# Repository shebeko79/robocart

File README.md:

### How not to build a robot:

https://youtu.be/LK63FLP5XUo

### References:
[Field Oriented Control (FOC) for stock hoverboards](https://github.com/EFeru/hoverboard-firmware-hack-FOC)

[Introduction to MaixCAM](https://wiki.sipeed.com/hardware/en/maixcam/maixcam.html)

[MaixCAM System Flashing](https://wiki.sipeed.com/hardware/en/maixcam/os.html)

[MaixPy Quick Start](https://wiki.sipeed.com/maixpy/doc/en/index.html)

[Install RNDIS driver](https://wiki.sipeed.com/hardware/en/maixsense/maixsense-a075v/install_drivers.html)

[Ultralytics quick start](https://docs.ultralytics.com/usage/python/)

[Tracking with Ultralytics](https://docs.ultralytics.com/modes/track/)

[FastSAM](https://docs.ultralytics.com/models/fast-sam/)

[Labeling Application](https://github.com/shebeko79/py_misc/tree/main/yolo_labeling)

[My YOLO train notes](https://github.com/shebeko79/py_misc/tree/main/yolo_train)

[Self-learning Tracker](https://wiki.sipeed.com/maixpy/doc/en/vision/self_learn_detector.html)

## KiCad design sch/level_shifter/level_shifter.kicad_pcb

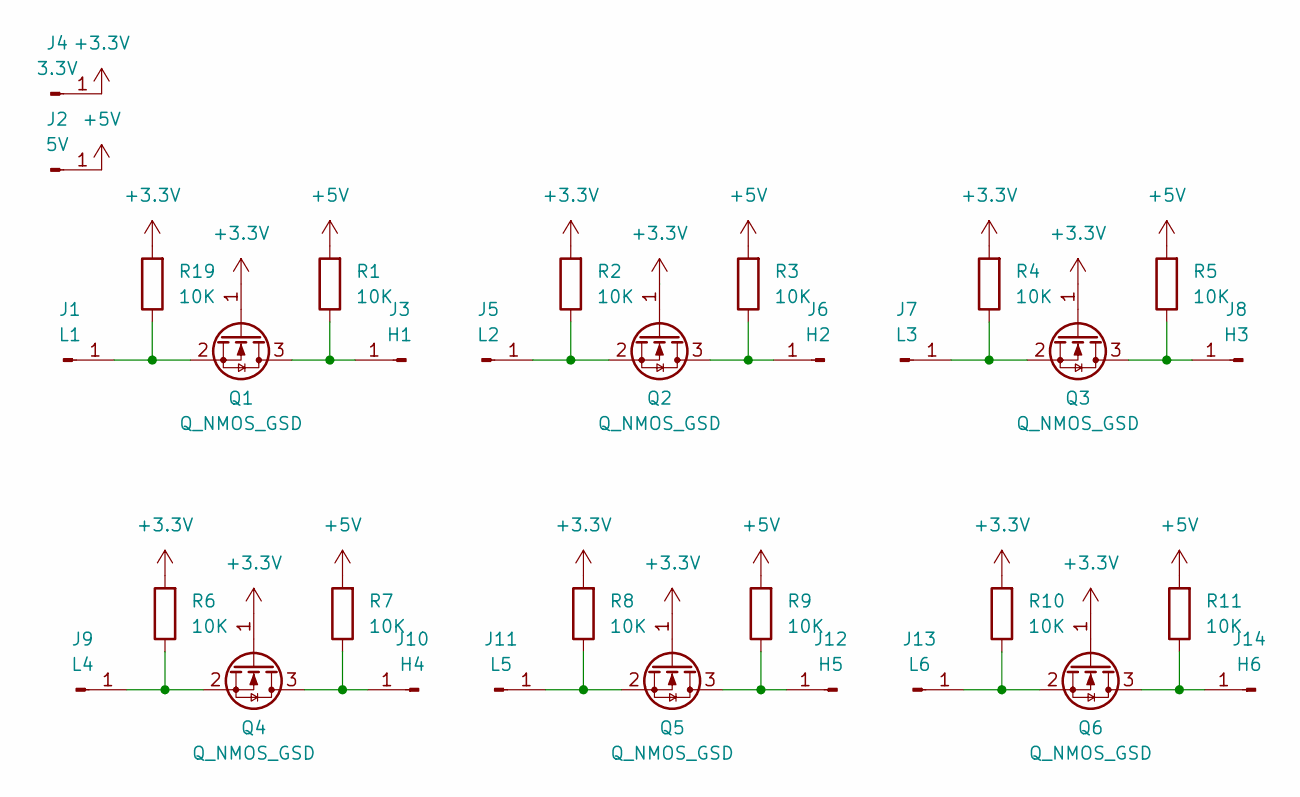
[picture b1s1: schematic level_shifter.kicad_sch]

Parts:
J1: L1; SolderWirePad_1x01_SMD_1x2mm
J2: 5V; SolderWirePad_1x01_SMD_1x2mm
J3: H1; SolderWirePad_1x01_SMD_1x2mm
J4: 3.3V; SolderWirePad_1x01_SMD_1x2mm
J5: L2; SolderWirePad_1x01_SMD_1x2mm
J6: H2; SolderWirePad_1x01_SMD_1x2mm
J7: L3; SolderWirePad_1x01_SMD_1x2mm
J8: H3; SolderWirePad_1x01_SMD_1x2mm
J9: L4; SolderWirePad_1x01_SMD_1x2mm
J10: H4; SolderWirePad_1x01_SMD_1x2mm
J11: L5; SolderWirePad_1x01_SMD_1x2mm
J12: H5; SolderWirePad_1x01_SMD_1x2mm
J13: L6; SolderWirePad_1x01_SMD_1x2mm
J14: H6; SolderWirePad_1x01_SMD_1x2mm
Q1, Q2, Q3, Q4, Q5, Q6: Q_NMOS_GSD; SOT-23_Handsoldering
R1, R2, R3, R4, R5, R6, R7, R8, R9, R10, R11, R19: 10K; R_0805_2012Metric

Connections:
+3.3V: J4.1, Q1.1 (G), Q2.1 (G), Q3.1 (G), Q4.1 (G), Q5.1 (G), Q6.1 (G), R2.2, R4.2, R6.2, R8.2, R10.2, R19.2
+5V: J2.1, R1.2, R3.2, R5.2, R7.2, R9.2, R11.2
unnamed: J1.1, Q1.2 (S), R19.1
unnamed: J3.1, Q1.3 (D), R1.1
unnamed: J5.1, Q2.2 (S), R2.1
unnamed: J6.1, Q2.3 (D), R3.1
unnamed: J7.1, Q3.2 (S), R4.1
unnamed: J8.1, Q3.3 (D), R5.1
unnamed: J9.1, Q4.2 (S), R6.1
unnamed: J10.1, Q4.3 (D), R7.1
unnamed: J11.1, Q5.2 (S), R8.1
unnamed: J12.1, Q5.3 (D), R9.1
unnamed: J13.1, Q6.2 (S), R10.1
unnamed: J14.1, Q6.3 (D), R11.1

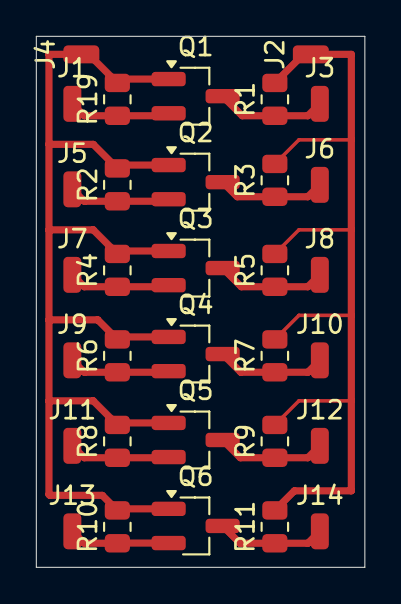
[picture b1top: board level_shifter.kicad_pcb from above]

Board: 4 copper layers, 18.2 x 29.5 mm, 32 parts (0 on the bottom side), 14 nets.

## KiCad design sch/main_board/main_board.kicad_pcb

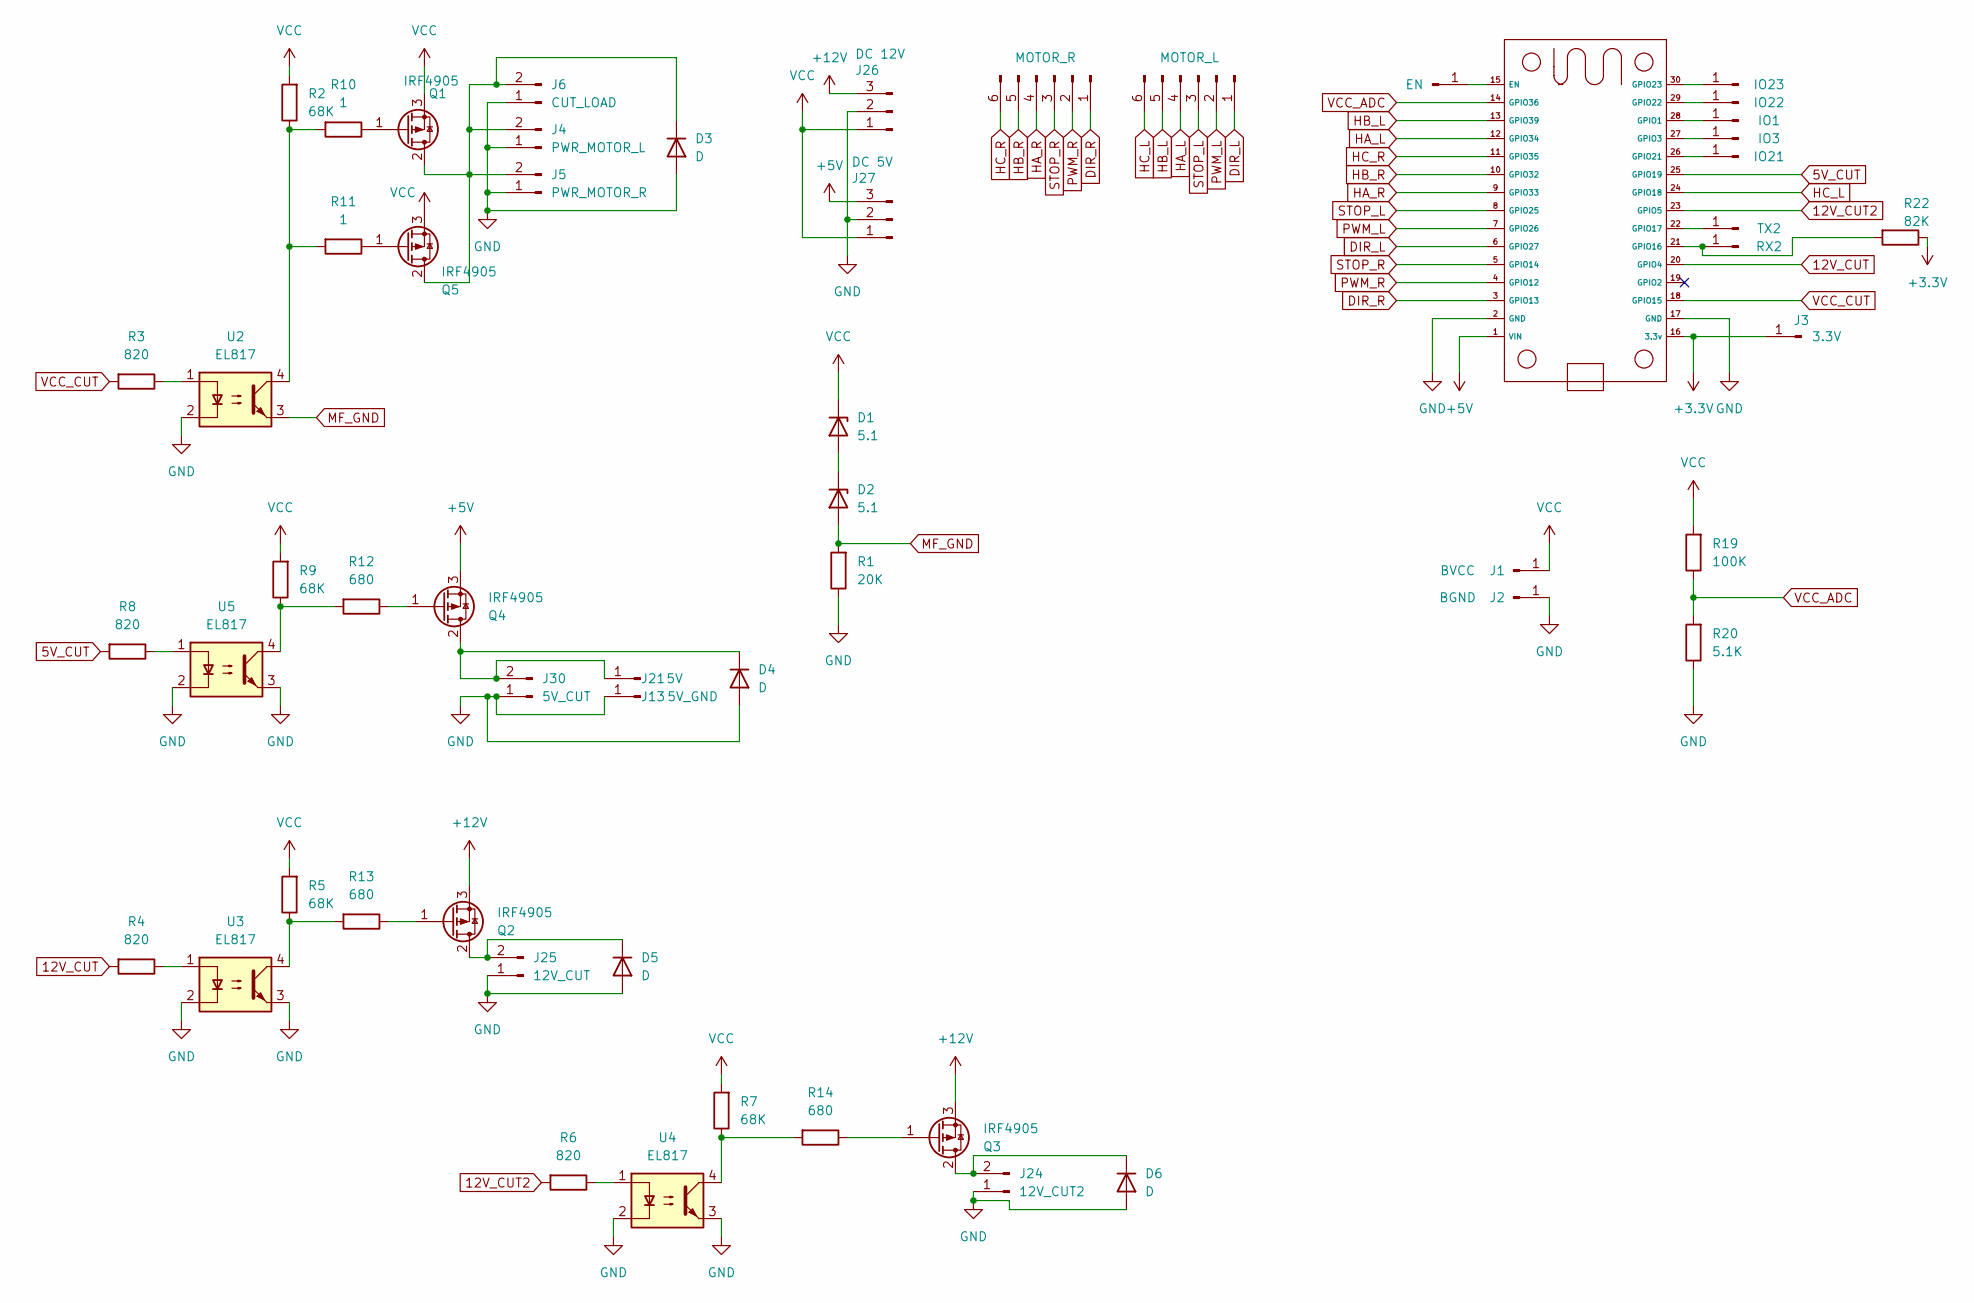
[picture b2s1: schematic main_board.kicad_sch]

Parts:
D1, D2: 5.1; D_5W_P12.70mm_Horizontal
D3, D4, D5, D6: D; D_2010_5025Metric_Pad1.52x2.65mm_HandSolder
J1: BVCC; SolderWirePad_1x01_SMD_4x8mm
J2: BGND; SolderWirePad_1x01_SMD_4x8mm
J3: 3.3V; SolderWirePad_1x01_SMD_2x4mm
J4: PWR_MOTOR_L; SolderWire-2.5sqmm_1x02_P7.2mm_D2.4mm_OD3.6mm
J5: PWR_MOTOR_R; SolderWire-2.5sqmm_1x02_P7.2mm_D2.4mm_OD3.6mm
J6: CUT_LOAD; SolderWire-2.5sqmm_1x02_P7.2mm_D2.4mm_OD3.6mm
J7: MOTOR_R; JST_XH_B6B-XH-A_1x06_P2.50mm_Vertical
J8: MOTOR_L; JST_XH_B6B-XH-A_1x06_P2.50mm_Vertical
J9: EN; SolderWirePad_1x01_SMD_1.5x3mm
J13: 5V_GND; SolderWirePad_1x01_SMD_2x4mm
J14: IO23; SolderWirePad_1x01_SMD_1.5x3mm
J15: IO22; SolderWirePad_1x01_SMD_1.5x3mm
J16: IO1; SolderWirePad_1x01_SMD_1.5x3mm
J17: IO3; SolderWirePad_1x01_SMD_1.5x3mm
J18: IO21; SolderWirePad_1x01_SMD_1.5x3mm
J21: 5V; SolderWirePad_1x01_SMD_2x4mm
J22: TX2; SolderWirePad_1x01_SMD_1.5x3mm
J23: RX2; SolderWirePad_1x01_SMD_1.5x3mm
J24: 12V_CUT2; SolderWire-1sqmm_1x02_P5.4mm_D1.4mm_OD2.7mm
J25: 12V_CUT; SolderWire-1sqmm_1x02_P5.4mm_D1.4mm_OD2.7mm
J26: DC 12V; SolderWire-1.5sqmm_1x03_P6mm_D1.7mm_OD3mm
J27: DC 5V; SolderWire-1.5sqmm_1x03_P6mm_D1.7mm_OD3mm
J30: 5V_CUT; SolderWire-1sqmm_1x02_P5.4mm_D1.4mm_OD2.7mm
Q1, Q2, Q3, Q4, Q5: IRF4905; TO-220-3_Vertical
R1: 20K; R_0805_2012Metric
R2, R5, R7, R9: 68K; R_0805_2012Metric
R3, R4, R6, R8: 820; R_0805_2012Metric
R10, R11: 1; R_0805_2012Metric
R12, R13, R14: 680; R_0805_2012Metric
R19: 100K; R_0805_2012Metric
R20: 5.1K; R_0805_2012Metric
R22: 82K; R_0805_2012Metric
U1: ESP32_30pin
U2, U3, U4, U5: EL817; SMDIP-4_W9.53mm

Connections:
5V_CUT: R8.2, U1.25 (GPIO19)
12V_CUT: R4.2, U1.20 (GPIO4)
12V_CUT2: R6.2, U1.23 (GPIO5)
+3.3V: J3.1, R22.1, U1.16 (3.3v)
+5V: J27.3, Q4.3 (S), U1.1 (VIN)
+12V: J26.3, Q2.3 (S), Q3.3 (S)
DIR_L: J8.1, U1.6 (GPIO27)
DIR_R: J7.1, U1.3 (GPIO13)
GND: D3.2 (A), D4.2 (A), D5.2 (A), D6.2 (A), J2.1, J4.1, J5.1, J6.1, J13.1, J24.1, J25.1, J26.2, J27.2, J30.1, R1.1, R20.1, U1.2 (GND), U1.17 (GND), U2.2, U3.2, U3.3, U4.2, U4.3, U5.2, U5.3
HA_L: J8.4, U1.12 (GPIO34)
HA_R: J7.4, U1.9 (GPIO33)
HB_L: J8.5, U1.13 (GPIO39)
HB_R: J7.5, U1.10 (GPIO32)
HC_L: J8.6, U1.24 (GPIO18)
HC_R: J7.6, U1.11 (GPIO35)
MF_GND: D2.2 (A), R1.2, U2.3
unnamed: D1.2 (A), D2.1 (K)
unnamed: D3.1 (K), J4.2, J5.2, J6.2, Q1.2 (D), Q5.2 (D)
unnamed: D4.1 (K), J21.1, J30.2, Q4.2 (D)
unnamed: D5.1 (K), J25.2, Q2.2 (D)
unnamed: D6.1 (K), J24.2, Q3.2 (D)
unnamed: J9.1, U1.15 (EN)
unnamed: J14.1, U1.30 (GPIO23)
unnamed: J15.1, U1.29 (GPIO22)
unnamed: J16.1, U1.28 (GPIO1)
unnamed: J17.1, U1.27 (GPIO3)
unnamed: J18.1, U1.26 (GPIO21)
unnamed: J22.1, U1.22 (GPIO17)
unnamed: J23.1, R22.2, U1.21 (GPIO16)
unnamed: Q1.1 (G), R10.1
unnamed: Q2.1 (G), R13.1
unnamed: Q3.1 (G), R14.1
unnamed: Q4.1 (G), R12.1
unnamed: Q5.1 (G), R11.1
unnamed: R3.1, U2.1
unnamed: R4.1, U3.1
unnamed: R6.1, U4.1
unnamed: R8.1, U5.1
unnamed: R2.1, R10.2, R11.2, U2.4
unnamed: R9.1, R12.2, U5.4
unnamed: R5.1, R13.2, U3.4
unnamed: R7.1, R14.2, U4.4
PWM_L: J8.2, U1.7 (GPIO26)
PWM_R: J7.2, U1.4 (GPIO12)
STOP_L: J8.3, U1.8 (GPIO25)
STOP_R: J7.3, U1.5 (GPIO14)
VCC: D1.1 (K), J1.1, J26.1, J27.1, Q1.3 (S), Q5.3 (S), R2.2, R5.2, R7.2, R9.2, R19.2
VCC_ADC: R19.1, R20.2, U1.14 (GPIO36)
VCC_CUT: R3.2, U1.18 (GPIO15)

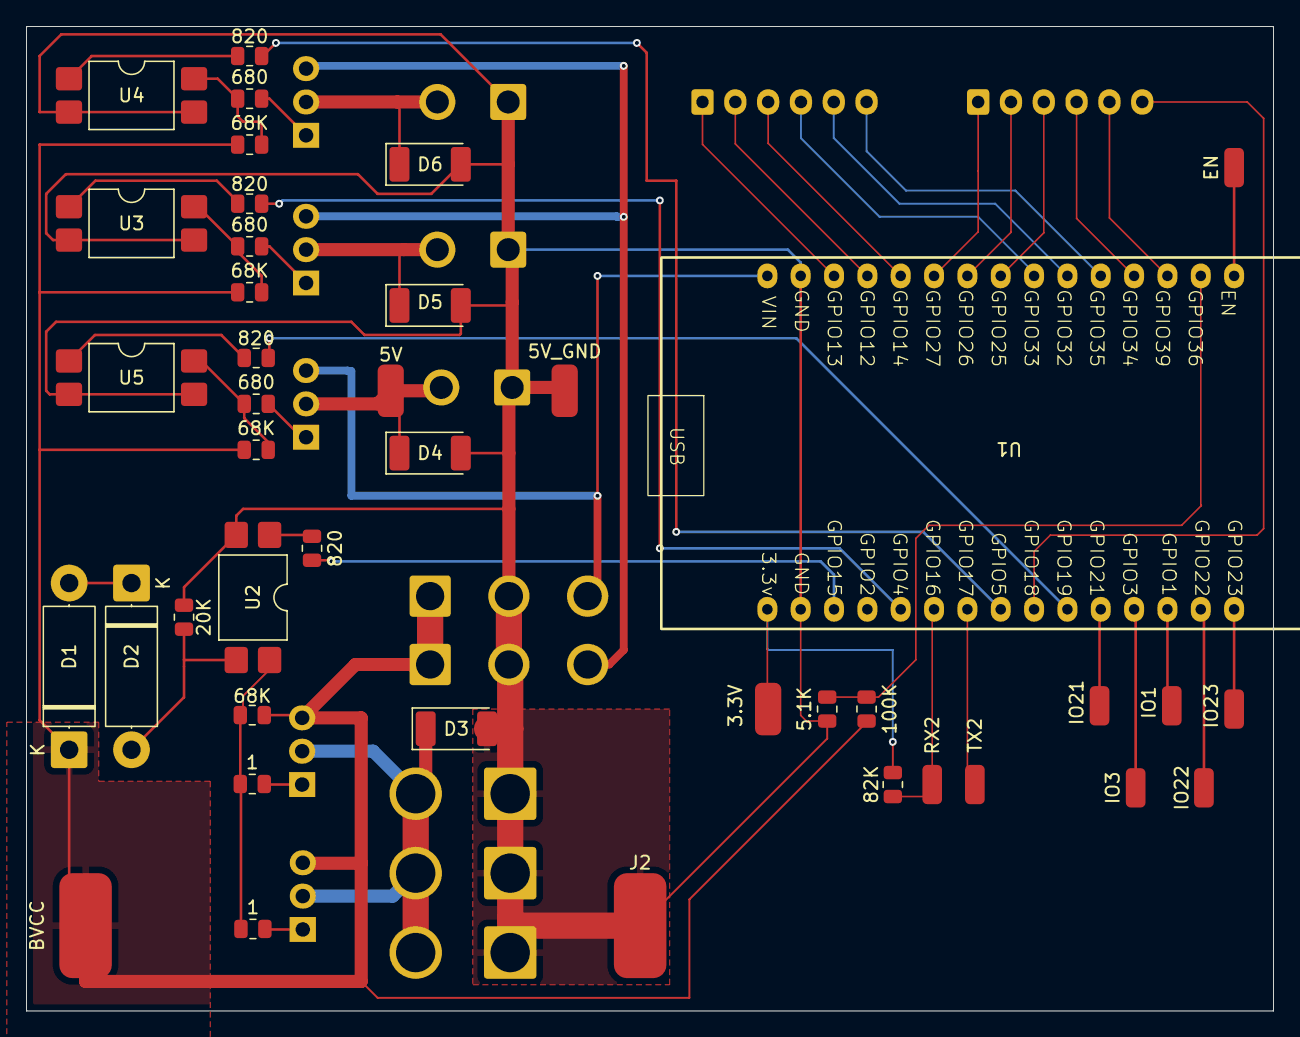
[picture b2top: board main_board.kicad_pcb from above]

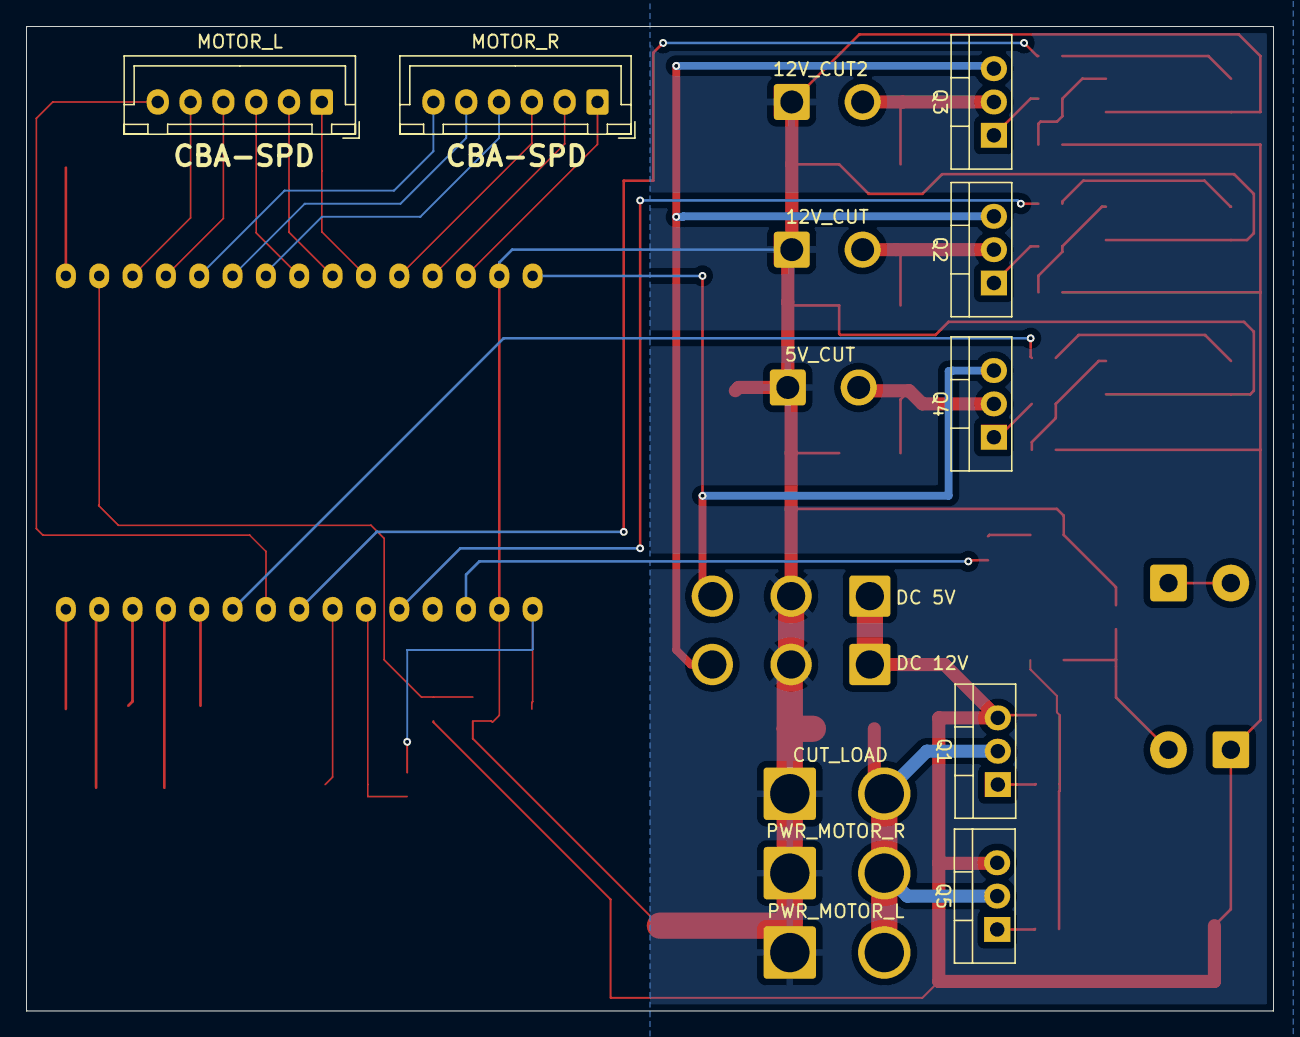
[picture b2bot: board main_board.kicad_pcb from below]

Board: 2 copper layers, 95.0 x 75.0 mm, 56 parts (15 on the bottom side), 49 nets.

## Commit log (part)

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2024-08-30 2 wheel platform based on esp32
2024-09-20 Bluetooth remote control
2024-09-28 Add "block" command in BT remote control
2024-09-28 Examples files for maixcam
2024-10-05 Implementing state machine for UI
2024-10-06 Implement button click and rectangle selection
2024-10-06 Add rectangle normalization
2024-10-07 Add MoveTo algo.
2024-10-12 returns image each second on web
2024-10-12 Add buttons using ChatGPT
2024-10-12 chatGPT image click
2024-10-12 chatGPT select rectangle
2024-10-12 1. Prevent rectangle visible until object selection (chatGPT) 2. Prevent dragging image (chatGPT) 3. Process requests on server side 4. Prevent crash, when to_jpeg() returns None after script restart
2024-10-12 Add just move states
2024-10-13 Mobile adaptation for select rectangle (chatGPT)
2024-10-13 Click on image for mobile (chatGPT)
2024-10-13 Move buttons to right
2024-10-13 Rename move states for vertical alignment Load main html from BASE_PATH path
2024-10-15 Add WiFi features. If fail connect to WiFi switch to AP mode
2024-10-19 Configuring network thru python was bad idea. Add S30wifidyn which try establish sta connection, if fails switch to ap mode
2024-10-19 Shrink move state to fit on a screen More robust S81robot stop function
2024-10-27 1. Get rid of Flask, because it creates a lot of threads and to noisy 2. Implement synchronized function call in main thread. 3. Get state just after click,click_point, sel_rect requests
2024-10-27 1. Apply immediately /click /click_point /sel_rect to buttons state 2. Return state even if requests are not executed 3. Move server to 80 port
2024-11-09 Increase line width to avoid red-grey rectangles
2024-11-19 pan\tilt stl model
2024-12-08 Parts schematic
2024-12-08 Test of zs-x11h controller
2024-12-09 rename motor.h to mdd3a controller which was used to control dc motor
2024-12-10 1. Move to PlatformIO 2. Speed measurement
2024-12-11 Connect brake pin
2024-12-12 Add PID control
2024-12-12 Change remote to relative protocol
2024-12-12 Add relative protocol
2024-12-13 1. Always brake for zero speed 2. 20kHz PWM just follow controllers recommendations 3. Separate RELATIVE_MAX_SPEED because it a bit scary with full speed 4. Dump wheels state in com port to have a gl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
2024-12-13 command to set maximum relative_speed
2024-12-13 Better command parsing
2024-12-21 Update 3d models 1. Base for pantilt 2. Cover for 2020 profile
2024-12-21 shorter screw placeholer
2024-12-25 Maixcam pinout
2024-12-28 Fix rotation cast
2024-12-28 Change mover to speed and pan
2024-12-31 Add scservo_sdk and pan_tilt example proba/pan_tilt.py all necessary function (i.e. reduce baud rate) which performes thru USB of SCServo controller maix/pan_tilt.py is a sketch for pan-til support
2025-01-01 Implementation of pan-tilt tracking Doesn't work as expected yet
2025-01-01 Add exit state for graceful exit
2025-01-02 Release servos when exit Measure real focus distance
2025-01-04 Full screen image
2025-01-05 1. Use relative (0.0-1.0) image coordinates for tracker 2. Make image full-screen on http page
2025-01-27 rtsp test
2025-01-27 Avoid low power exception on shutdown
2025-01-27 send file feature Potentially unsafe we need to check if file really in assets directory
2025-02-16 PID control on pwm instead of speed
2025-02-16 Split motor_speed.h to .cpp and .h
2025-02-16 Try to make remote more stable
2025-02-16 Assume we have some koef. between PWM and unloaded wheel speed. Make error correction around this value. Also introduced delays. But it doesn't look like it helps somehow. Add maximum acceleration bu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
2025-02-16 Motors control in separate thread
2025-03-08 Speed test with different masses and PWM
2025-03-14 Temoprary checkpoint
2025-03-15 Less or more satisfied. Works pretty much the same for different loads. Like empty truck or me as a load. We don't try to adjust m_speed2pwm because it not constant even for the same environment. In 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
    The general idea now is:
    - adjust PWM slowly unless it increase the speed with any acceleration
    - add one time kick to PWM if speed remain zero
    - break if speed go to far in wrong direction or go with acceleration
2025-03-22 rename timer0 to speed_timer
2025-03-22 Increase pan/tilt insensitive zone to avoid shaking
2025-03-30 Yolo custom model track
2025-04-19 Hide internal tracker structure
2025-04-19 Implement yolo trackers
2025-04-21 Add pan, move, follow tracking modes.
2025-04-21 Caption for tracker selection
2025-04-21 Show click caption and rectangle caption in HTML
2025-04-21 Fix X offset in point and rectangle selection. Wrong condition cause default 640X480 doesn't update to real size 640X640
2025-04-21 Fix nanotrack display on the screen
2025-04-23 1. Pass correct fit to MoveTo 2. Ensure tracker still in the yolo_trackers, because self stopping algo calls YoloTrackObject::stop() 2 times.
2025-09-29 Discover different streaming options
2025-09-29 Kikad board of the robot
2025-10-12 1. Add pins header 2. Add deep sleep on low-voltage
2025-10-13 Tune voltage for another ESP module
2025-10-13 1. Reconnect 5V_CUT from GPIO2 to GPIO19. Because GPIO2 is the LED 2. Pull-up RX2 3. Figured out with VCC_ADC resistor divider 4. Change input to NPN cut transistor from 200 Om to 10K. 200 Om is way 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
2025-10-13 Swap the motors. Simply because it easier to connect
2025-11-16 Final scheme changes before production
2025-11-24 5V <-> 3.3V level shifter schematic Direct 5V on other inputs affects on ADC and we can't get correct voltage
2025-11-24 Smoothing voltage and add delay on low voltage sleep
2025-11-24 I don't use this N-MOSFET anymore
2025-11-25 We can't use GPIO39 for hall input, because it also VN Whenever we measure ADC on GPIO36 (VP) interrupt for GPIO39 is raised
2025-11-25 .kikad_prl is a settings. Don't need to store'em in repository
2025-11-29 Use hall sensors to detect direction of speed
2025-11-29 Move hardware specific from speed controller directly to motor controller
2025-11-29 Add state,sleep,power commands
2025-11-30 Show voltage on a screen and web interface
2025-11-30 Increase a low voltage a bit, because not much energy left even to sleep with previous limit.
2025-12-13 Move touch functionality out of main.py into separate file
2025-12-13 1. Fix: sleep command should receive int parameter 2. Increase sleep duration to 5 min, because unlikely battery charge faster
2025-12-13 Go to sleep on idle
2025-12-13 Add Telegram support
2025-12-14 Seems times updates after start. And because of previous attempt to fix it module doesn't off at all
2025-12-14 Graceful power down
2025-12-14 Save config and last telegram update_id to files
2025-12-14 Need to skip few cycles to let receive the voltage and get stable image
2025-12-14 Adaptive telegram update interval
2025-12-15 Check that commands has been sent from our chat
2025-12-15 Treat telegram commands also as keep alive factor
2025-12-16 fix params duplication for set of commands
2025-12-19 send/receive jpg just throu UDP
2025-12-20 Trying to establish p2p connection. Fails so far
2025-12-25 Start implementing UDP channel
2025-12-28 Start implementing desktop application Fix some bugs in UDP protocol
2025-12-29 First image in the client application
2025-12-31 Switch off http interface
2025-12-31 Change default net name to "robocart"
2025-12-31 Better image flow control with ackceptance
2025-12-31 Add move camera and cart commands
2026-01-01 Process state response
2026-01-01 Break connection on timeout
2026-01-02 Enable arrow keys Arrow keys only intercepted if main_widget is focused and arrow keys doesn't work as focus change
2026-01-02 Camera view button
2026-01-02 Add dynamic buttons
2026-01-04 Udp packets maintains keep alive
2026-01-04 Add watchdog timer
2026-01-06 ip command for telegram
2026-01-06 Support of IPv6
2026-01-10 Add AES. AES crypts really slow on maix. Probably I have to find more practical solution.
2026-01-11 1. Avoid intermediate memory allocation in pack() 2. Reduce maximim jpeg quailty and reducejpeg step to 1 to avoid skipped frames 3. Check packet inside parse() because otherwise we can't check it pr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
2026-01-11 Pack chunk just in common pack() function to avoid additional memory allocation and copy
2026-01-11 Remove Pan, Move actions from the main state in the application. Because exactly the same controls already available
2026-02-15 Pure AES and CRC are ridiculously slow. Instead of real AES-CTR I generate nonce and use it as starting number for each packet. Thus I can make one xor-sequence for every packet. And use numpy to xor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
2026-02-20 Add udp_relay mode into device
2026-02-21 Run udprelay on server
2026-02-28 1. Put JPEG quality into constant 2. If we can't parse packet we can't count it for timeout. Same as in udp_client.py
2026-02-28 Initial implementation of chunked image transmit. Without testing yet
2026-02-28 Split aes_pack and its test
2026-03-01 packet_processor test
2026-03-01 tune JPEG size
2026-03-02 Tune JPEG
2026-03-02 Push all chunks at a time
2026-03-21 Connect to local name first, then use relay
2026-03-21 Free mode for camera pan, tilt.
2026-04-09 Just stupid update of environment
2026-04-17 Fix misspelling
2026-04-19 Just change examples
2026-04-23 1. Left wifi STA mode active if AP is not required 2. Restart DHCP on WiFi connected
2026-04-23 1. Fix error if no local_name provided 2. Print receiving packet delay
2026-04-23 Select all YOLO objects for tracking. Just sort confident first
2026-04-27 1. Add distance command 2. Add traveled distance to state output 3. State commands also prevents failSafe() 4. Increase a bit FAIL_SAFE_DELAY because bluetooth can't send state command in time
2026-04-29 Android application generated by cursor
2026-04-30 Load of udp.key Cursor code
2026-04-30 Add connection thru relay server Cursor code
2026-04-30 Status bar to the bottom Cursor
2026-04-30 1. Different layout for horizontal and vertical mode (Cursor) 2. Changed layout for direction butttons
2026-05-01 1. Different icon for relay mode (cursor) 2. Latency update in the status bar (cursor)
2026-05-01 Latency update (cursor)
2026-05-01 Fixed bug with rectangle freeze (cursor)
2026-05-01 Filter Pan and Move states (cursor)
2026-05-01 Keep screen always on (cursor)
2026-05-05 Buttons in application interface calls distance command
2026-05-07 Moved from arduino project
2026-05-07 Test if we can detect the speed using CPU cycles count
2026-05-08 Compare speed measurement using timer an cpu cycles method
2026-05-08 Compare how fast different methods reacts to speed change
2026-05-09 Check cpu speed deviation on different PWM
2026-05-10 Smoothing cpu cycles by 3 test
2026-05-11 1. Move to CPU cycles speed detection method 2. Increase PWM resolution to 10 bits
2026-05-17 Speed detection improvement. If we got fired the first hall sensor isr, we already can assume some speed using known delay between check_speed_timeout() calls.
2026-05-23 Calculate blind period for such speed
2026-05-25 Bell shape base for pan-tilt
2026-05-26 Calculate just correction in addition to main speed function
2026-05-26 Use snapshots of parameters for speed control
2026-05-27 Detect blind interval
2026-05-30 Find out that 110ms is enough to remove stalled protection of motor controller
2026-05-30 Find out kick pwm doesn't really affect how unloaded wheel speed up from zero to 0.3m/s
2026-05-30 Speed hangs because of MAIN_CYCLE_DELAY if we got only one hall sensor event
2026-05-30 1. Anti stall 2. Remove brake on direction change calc_pwm() works pretty well
2026-05-31 We don't need detach/atach pwm pin we can just set pwm to zero
2026-05-31 Remove brake_state because noobody need it
2026-05-31 1. Add MIN_PWM to avoid motor controller zero speed protection 2. Add PWM limiter. The idea is we just limit maximum power.
2026-06-06 decode() might cause an exception
2026-06-06 blind point near zero speed and zero turn
2026-06-06 Hint brake if m_dst_speed == 0
2026-06-09 Add esp_now for remote control
2026-06-14 cover parts rebuilt for soft plastic
2026-06-27 Convert using opencv from YVU420SP to RGB example
